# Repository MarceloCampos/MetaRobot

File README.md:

# MetaRobot

Arquivos KiCad da placa de circuito impresso / base do robô MetaRobot
página Wiki do Garoa HC: https://garoa.net.br/wiki/Meta_Robot

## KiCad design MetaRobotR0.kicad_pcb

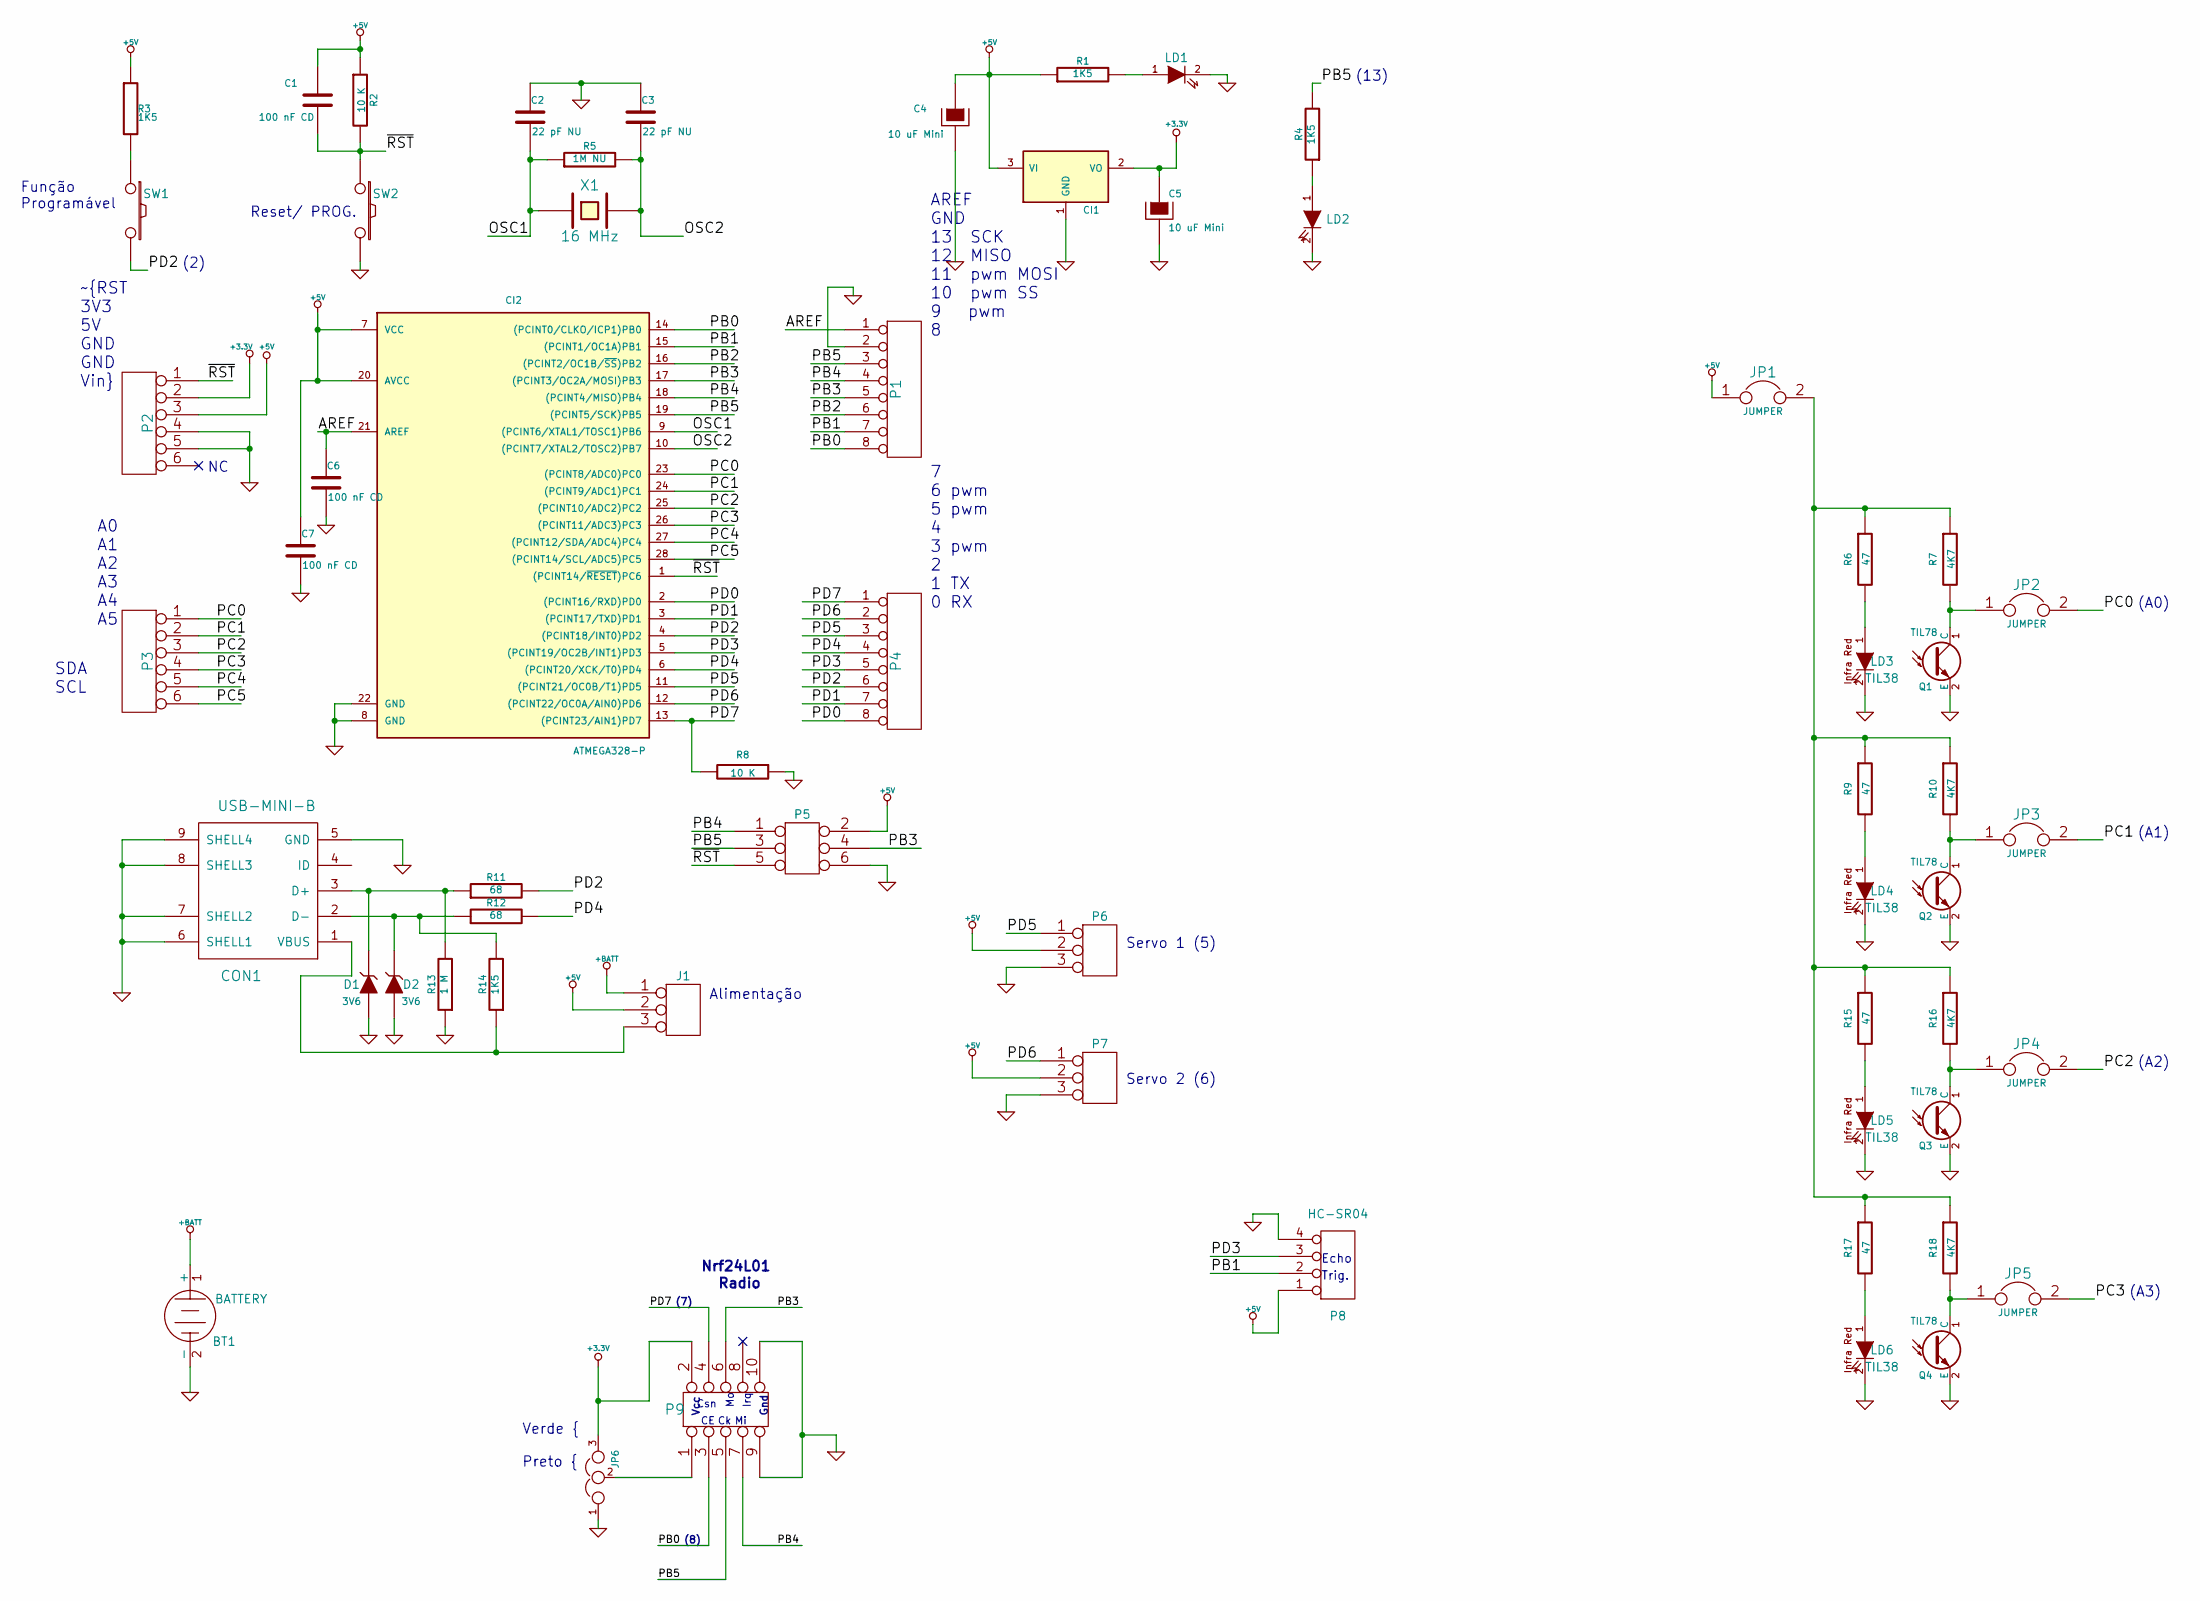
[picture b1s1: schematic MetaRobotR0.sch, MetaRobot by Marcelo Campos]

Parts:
BT1: BATTERY
C1, C6, C7: 100 nF CD
C2, C3: 22 pF NU
C4, C5: 10 uF Mini
CI1: NCP1117 3V3 NU
CI2: ATMEGA328-P; DIL28
CON1: USB-MINI-B
D1, D2: 3V6
J1: CONN_3
JP1, JP2, JP3, JP4, JP5: JUMPER
JP6: JUMPER3
LD1: Vd 3mm
LD2: Vm 3mm
LD3, LD4, LD5, LD6: TIL38
P1, P4: CONN_8
P2, P3: CONN_6
P5: CONN_3X2
P6, P7: CONN_3
P8: HC-SR04
P9: CONN_5X2 NU
Q1, Q2, Q3, Q4: TIL78
R1, R3, R4, R14: 1K5
R2, R8: 10 K
R5: 1M NU
R6, R9, R15, R17: 47
R7, R10, R16, R18: 4K7
R11, R12: 68
R13: 1 M
SW1, SW2: SW Mini 180o
X1: 16 MHz

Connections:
+3.3V: C5.1, CI1.2 (VO), JP6.3, P2.2, P9.2
+5V: C1.1, C4.1, C7.1, CI1.3 (VI), CI2.7 (VCC), CI2.20 (AVCC), J1.2 (PM), JP1.1, P2.3, P5.2, P6.2 (PM), P7.2 (PM), P8.1, R1.1, R2.1, R3.1
+BATT: BT1.1 (+), J1.1
/AREF: C6.1, CI2.21 (AREF), P1.1
/OSC1: C2.2, CI2.9 ((PCINT6/XTAL1/TOSC1)PB6), R5.1, X1.1
/OSC2: C3.2, CI2.10 ((PCINT7/XTAL2/TOSC2)PB7), R5.2, X1.2
/PB0: CI2.14 ((PCINT0/CLKO/ICP1)PB0), P1.8, P9.3
/PB1: CI2.15 ((PCINT1/OC1A)PB1), P1.7, P8.2
/PB2: CI2.16 ((PCINT2/OC1B/~SS~)PB2), P1.6
/PB3: CI2.17 ((PCINT3/OC2A/MOSI)PB3), P1.5, P5.4, P9.6
/PB4: CI2.18 ((PCINT4/MISO)PB4), P1.4, P5.1, P9.7
/PB5: CI2.19 ((PCINT5/SCK)PB5), P1.3, P5.3, P9.5, R4.2
/PC0: CI2.23 ((PCINT8/ADC0)PC0), JP2.2, P3.1
/PC1: CI2.24 ((PCINT9/ADC1)PC1), JP3.2, P3.2
/PC2: CI2.25 ((PCINT10/ADC2)PC2), JP4.2, P3.3
/PC3: CI2.26 ((PCINT11/ADC3)PC3), JP5.2, P3.4
/PC4: CI2.27 ((PCINT12/SDA/ADC4)PC4), P3.5
/PC5: CI2.28 ((PCINT14/SCL/ADC5)PC5), P3.6
/PD0: CI2.2 ((PCINT16/RXD)PD0), P4.8
/PD1: CI2.3 ((PCINT17/TXD)PD1), P4.7
/PD2: CI2.4 ((PCINT18/INT0)PD2), P4.6, R11.2, SW1.2
/PD3: CI2.5 ((PCINT19/OC2B/INT1)PD3), P4.5, P8.3
/PD4: CI2.6 ((PCINT20/XCK/T0)PD4), P4.4, R12.2
/PD5: CI2.11 ((PCINT21/OC0B/T1)PD5), P4.3, P6.1
/PD6: CI2.12 ((PCINT22/OC0A/AIN0)PD6), P4.2, P7.1
/PD7: CI2.13 ((PCINT23/AIN1)PD7), P4.1, P9.4, R8.2
/~RST: C1.2, CI2.1 ((PCINT14/~RESET~)PC6), P2.1, P5.5, R2.2, SW2.1
GND: BT1.2 (-), C2.1, C3.1, C4.2, C5.2, C6.2, C7.2, CI1.1 (GND), CI2.8 (GND), CI2.22 (GND), CON1.5 (GND), CON1.6 (SHELL1), CON1.7 (SHELL2), CON1.8 (SHELL3), CON1.9 (SHELL4), D1.1 (A), D2.1 (A), JP6.1, LD1.2 (K), LD2.2 (K), LD3.2 (K), LD4.2 (K), LD5.2 (K), LD6.2 (K), P1.2, P2.4, P2.5, P5.6, P6.3, P7.3, P8.4, P9.9, P9.10, Q1.2 (E), Q2.2 (E), Q3.2 (E), Q4.2 (E), R8.1, R13.1, SW2.2
unnamed: R3.2, SW1.1
unnamed: JP6.2, P9.1
unnamed: LD1.1 (A), R1.2
unnamed: JP4.1, Q3.1 (C), R16.2
unnamed: LD6.1 (A), R17.2
unnamed: JP5.1, Q4.1 (C), R18.2
unnamed: JP2.1, Q1.1 (C), R7.2
unnamed: LD4.1 (A), R9.2
unnamed: JP3.1, Q2.1 (C), R10.2
unnamed: LD5.1 (A), R15.2
unnamed: CON1.3 (D+), D1.2 (K), R11.1, R13.2
unnamed: CON1.2 (D-), D2.2 (K), R12.1, R14.2
unnamed: CON1.1 (VBUS), J1.3, R14.1
unnamed: JP1.2, R6.1, R7.1, R9.1, R10.1, R15.1, R16.1, R17.1, R18.1
unnamed: LD3.1 (A), R6.2
unnamed: LD2.1 (A), R4.1

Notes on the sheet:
Alimentação
Reset/ PROG.
Servo 1 (5)
Servo 2 (6)
A0 A1 A2 A3 A4 A5
~RST 3V3 5V GND GND Vin
7 6 pwm 5 pwm 4 3 pwm 2 1 TX 0 RX
AREF GND 13 SCK 12 MISO 11 pwm MOSI 10 pwm SS 9 pwm 8
SDA SCL
(A0)
(A1)
(A2)
(A3)
Vcc
Gnd
(8)
Csn
Irq
(7)
Nrf24L01
Radio
Função Programável
(2)
(13)
Trig.
Echo
Verde { Preto {

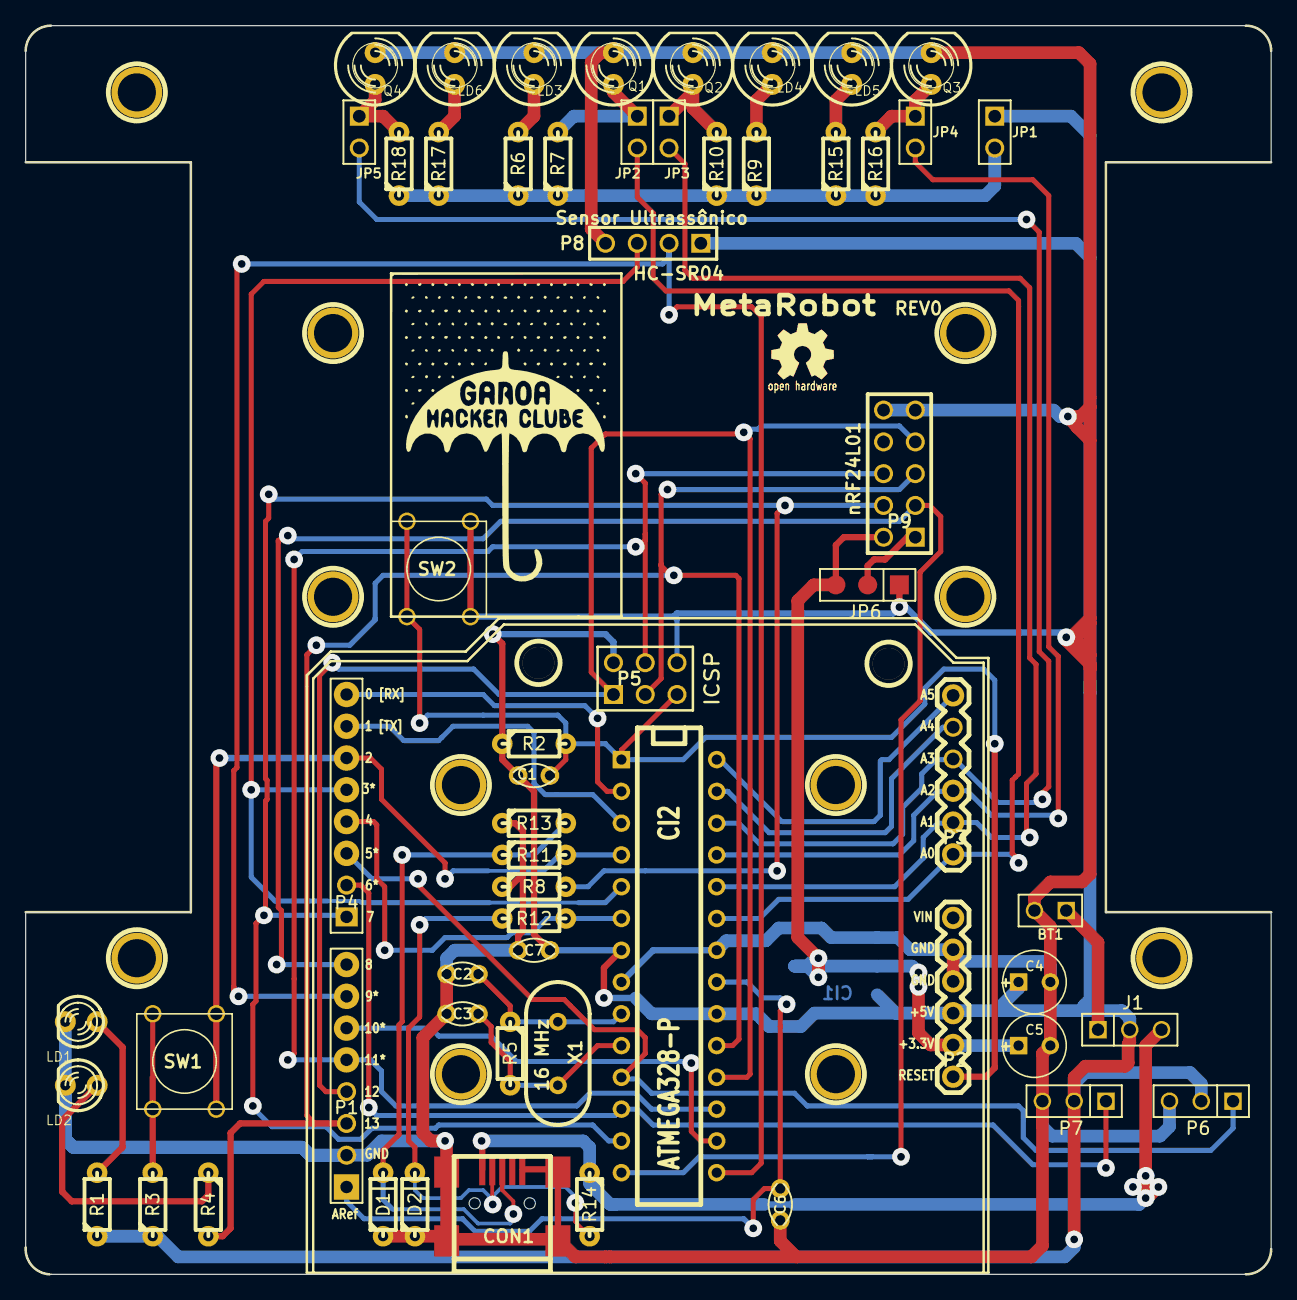
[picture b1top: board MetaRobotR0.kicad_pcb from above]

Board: 2 copper layers, 99.6 x 99.8 mm, 75 parts (1 on the bottom side), 44 nets.

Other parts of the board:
1PIN, 1PIN#2, 1PIN#3, 1PIN#4, 1PIN#5, 1PIN#6, 1PIN#7, 1PIN#8, 1PIN#9, 1PIN#10, 1PIN#11, 1PIN#12: P***; 1pin
L1: LOGO
V4, V5: 1pin

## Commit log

2016-03-16 Added files via upload
